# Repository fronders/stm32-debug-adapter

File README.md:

View this project on [CADLAB.io](https://cadlab.io/project/2519). 

# STM32 Debug Adapter Board

Adapter for various SWD programmers for STM32. 

<br />

This repo contains:
- Autodesk Eagle CAD v9 project
- PDF schematic & board layout
- Gerber files (in PCBWay-compatible format: RS-274X + Excellon)

What's here in README:
- [Supported STM32 programmers](#Supported-STM32-programmers)
- [Interfaces pinout](#Interfaces-pinout)
	- [Original ST-Link V2 by STMicroelectronics](#Original-ST-Link-V2-by-STMicroelectronics)
	- [J-Link by SEGGER](#J-Link-by-SEGGER)
	- [Chinese ST-Link V2 dongle](#Chinese-ST-Link-V2-dongle)
	- [Chinese MX-Link dongle](#Chinese-MX-Link-dongle)
	- [Nucleo-32 original ST-Link V2-1 by STMicroelectronics](#Nucleo-32-original-ST-Link-V2-1-by-STMicroelectronics)
	- [Nucleo-64 original ST-Link V2-1 by STMicroelectronics](#Nucleo-64-original-ST-Link-V2-1-by-STMicroelectronics)
	- [Nucleo-144 original ST-Link V2-1 by STMicroelectronics](#Nucleo-144-original-ST-Link-V2-1-by-STMicroelectronics)
	- [Blue Pill board (STM32F103C8T6)](#Blue-Pill-board-(STM32F103C8T6))
	- [Black Pill board (STM32F103C8T6)](#Black-Pill-board-(STM32F103C8T6))
	- [Tag-Connect 6 Pin Cable (TC2030-IDC)](#Tag-Connect-6-Pin-Cable-(TC2030-IDC))
- [Rev. B board info](#Rev.-B-board-info-(latest))
- [Rev. A board info](#Rev.-A-board-info)
- [Original board info](#Original-board-info)

<hr />

## Supported STM32 programmers

- Original ST-Link V2 by STMicroelectronics
- Nucleo original ST-Link V2-1 by STMicroelectronics
- Chinese ST-Link V2 clones (2 versions: ST-Link & MX-Link - different pinouts)
- J-Link by SEGGER

<hr />

## Interfaces pinout

### Original ST-Link V2 by STMicroelectronics

STM32 connector pinout:

| Name | Pin | Pin | Name |
| ---: | :---: | :---: | :--- |
| VDD_TRGT | 1 | 2 | VDD_TRGT |
| NC | 3 | 4 | GND |
| NC | 5 | 6 | GND |
| SWDIO | 7 | 8 | GND |
| SWCLK | 9 | 10 | GND |
| NC | 11 | 12 | GND |
| SWO | 13 | 14 | GND |
| NRST | 15 | 16 | GND |
| NC | 17 | 18 | GND |
| 3.3V | 19 | 20 | GND | 

### J-Link by SEGGER

Target connector pinout:

| Name | Pin | Pin | Name |
| ---: | :---: | :---: | :--- |
| 3.3V | 1 | 2 | NC |
| NC | 3 | 4 | GND |
| NC | 5 | 6 | GND |
| SWDIO | 7 | 8 | GND |
| SWCLK | 9 | 10 | GND |
| NC | 11 | 12 | GND |
| SWO | 13 | 14 | GND |
| NRST | 15 | 16 | GND |
| NC | 17 | 18 | GND |
| 5V | 19 | 20 | GND

### Chinese ST-Link V2 dongle

SWD connector pinout:

| Name | Pin | Pin | Name |
| ---: | :---: | :---: | :--- |
| RST\* | 1 | 2 | SWDIO |
| GND | 3 | 4 | GND |
| SWO\* | 5 | 6 | SWCLK |
| 3.3V | 7 | 8 | 3.3V |
| 5V\*\* | 9 | 10 | 5V\*\*

\* - not connected on the device, need to modify ST-Link: cut STM8's tracks for nRST & SWIM signals to become instead STM32's nRST (STM32 pin 18) & SWO (STM32 pin 31) signals

\*\* - not connected on adapter board

### Chinese MX-Link dongle

SWD connector pinout:

| Name | Pin | Pin | Name |
| ---: | :---: | :---: | :--- |
| RST\* | 1 | 2 | SWCLK |
| SWO\* | 3 | 4 | SWDIO |
| GND | 5 | 6 | GND |
| 3.3V | 7 | 8 | 3.3V |
| 5V\*\* | 9 | 10 | 5V\*\*

\* - not connected on the device, need to modify MX-Link: cut STM8's tracks for nRST & SWIM signals to become instead STM32's nRST (STM32 pin 18) & SWO (STM32 pin 31) signals

\*\* - not connected on adapter

### Nucleo-32 original ST-Link V2-1 by STMicroelectronics

CN2 connector pinout:

| Name | Pin | Pin | Name |
| ---: | :---: | :---: | :--- |
| - | - | 5 | NC |
| 3.3V | 4 | 3 | SWCLK |
| GND | 2 | 1 | SWDIO

### Nucleo-64 original ST-Link V2-1 by STMicroelectronics

CN4 connector pinout:

| Pin | Name |
| ---: | :--- |
| 1 | VDD_TRGT |
| 2 | SWCLK |
| 3 | GND |
| 4 | SWDIO |
| 5 | NRST |
| 6 | SWO

### Nucleo-144 original ST-Link V2-1 by STMicroelectronics

CN6 connector pinout:

| Pin | Name |
| ---: | :--- |
| 1 | VDD_TRGT |
| 2 | SWCLK |
| 3 | GND |
| 4 | SWDIO |
| 5 | NRST |
| 6 | SWO

### Blue Pill board (STM32F103C8T6)

Programming connector pinout:

| Pin | Name |
| ---: | :--- |
| 1 | GND |
| 2 | SWCLK |
| 3 | SWDIO |
| 4 | 3.3V

### Black Pill board (STM32F103C8T6)

Programming connector pinout:

| Pin | Name |
| ---: | :--- |
| 1 | GND |
| 2 | SWCLK |
| 3 | SWDIO |
| 4 | 3.3V

### Tag-Connect 6 Pin Cable (TC2030-IDC)

<br />

IDC-6 connector pinout:

| Name | Pin | Pin | Name |
| ---: | :---: | :---: | :--- |
| 3.3V | 1 | 2 | SWDIO |
| NRST | 3 | 4 | SWCLK |
| GND | 5 | 6 | SWO

<hr />

## Rev. B board info (latest)

PDF schematic & board:
- [Rev. B single file](pdf/rev.B/stm32%20debug%20adapter%20rev.B.pdf)
- [Rev. B schematic](pdf/rev.B/stm32%20debug%20adapter%20rev.B%20sch.pdf)
- [Rev. B board](pdf/rev.B/stm32%20debug%20adapter%20rev.B%20brd.pdf)

Solder jumper can be used with Original ST-Link to connect IDC-20 pin 19 VDD (3.3V) to rest of 3.3V (pins 1-2). **Jumper should remain open for use with J-Link, it has 3.3V output on pin 1, while pin 19 has 5V, might damage your board!**

Changes:
- Changed SWD pin header to match Nucleo ST-Link V2-1 pinout
- Fixed Blue Pill / Black Pill board (STM32F103C8T6) connector to be non-mirrored
- Added a solder jumper (NO) between pin 19 and pins 1-2 for Original ST-Link V2 to provide 3.3V power
- Added power indicator LED

Supported interfaces:
- Chinese ST-Link V2 dongle
- Chinese MX-Link dongle
- J-Link / Original ST-Link V2
- Tag-Connect (TC2030-IDC)
- Nucleo original ST-Link V2-1
- Blue Pill / Black Pill board

Known issues:
- none

<hr />

## Rev. A board info

PDF schematic & board:
- [Rev. A single file](pdf/rev.A/stm32%20debug%20adapter%20rev.A.pdf)
- [Rev. A schematic](pdf/rev.A/stm32%20debug%20adapter%20rev.A%20sch.pdf)
- [Rev. A board](pdf/rev.A/stm32%20debug%20adapter%20rev.A%20brd.pdf)

Changes:
- Added Blue Pill / Black Pill board (STM32F103C8T6) connector

Supported interfaces:
- Chinese ST-Link V2 dongle
- Chinese MX-Link dongle
- J-Link / Original ST-Link V2
- Tag-Connect (TC2030-IDC)
- SWD pin header
- Blue Pill / Black Pill board

Known issues:
- Blue Pill header mirrored, **need to plug in board upside down (chip facing down)**
- Original ST-Link V2 does not provide 3.3V on pins 1-2 (it is VDD_Target input instead), need to connect pin 19 to pins 1-2 on IDC-20 connector with external wire. J-Link works okay, as pin 1 has 3.3V output.

<hr />

## Original board info

PDF schematic & board:
- [Original schematic](pdf/original/stm32%20debug%20adapter%20sch.pdf)

Supported interfaces:
- Chinese ST-Link V2 dongle
- Chinese MX-Link dongle
- J-Link / Original ST-Link V2
- Tag-Connect (TC2030-IDC)
- SWD pin header

Known issues:
- Original ST-Link V2 does not provide 3.3V on pins 1-2 (it is VDD_Target input instead), need to connect pin 19 to pins 1-2 on IDC-20 connector with external wire. J-Link works okay, as pin 1 has 3.3V output.

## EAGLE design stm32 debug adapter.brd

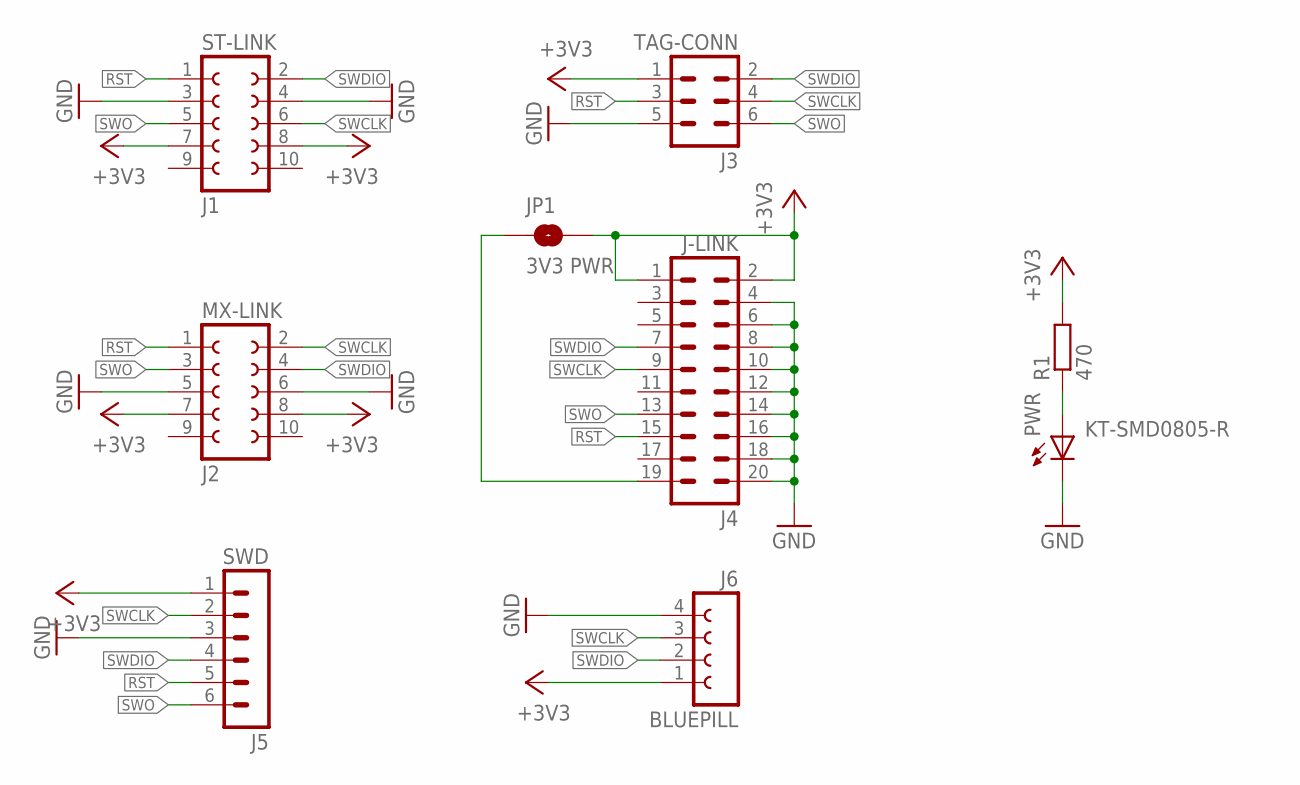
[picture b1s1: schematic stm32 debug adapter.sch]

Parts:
J1: ST-LINK; FE05-2W
J2: MX-LINK; FE05-2W
J3: TAG-CONN; ML6
J4: J-LINK; ML20
J5: SWD; MA06-1
J6: BLUEPILL; FE04W
JP1: 3V3 PWR; SMT-JUMPER_2_NO_NO-SILK
PWR: KT-SMD0805-R; SML0805
R1: 470; R0805

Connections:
3V3PWR: J4.19, JP1.1
+3V3: J1.7, J1.8, J2.7, J2.8, J3.1, J4.1, J4.2, J5.1, J6.1, JP1.2, R1.2
GND: J1.3, J1.4, J2.5, J2.6, J3.5, J4.4, J4.6, J4.8, J4.10, J4.12, J4.14, J4.16, J4.18, J4.20, J5.3, J6.4, PWR.C
unnamed: PWR.A, R1.1
RST: J1.1, J2.1, J3.3, J4.15, J5.5
SWCLK: J1.6, J2.2, J3.4, J4.9, J5.2, J6.3
SWDIO: J1.2, J2.4, J3.2, J4.7, J5.4, J6.2
SWO: J1.5, J2.3, J3.6, J4.13, J5.6

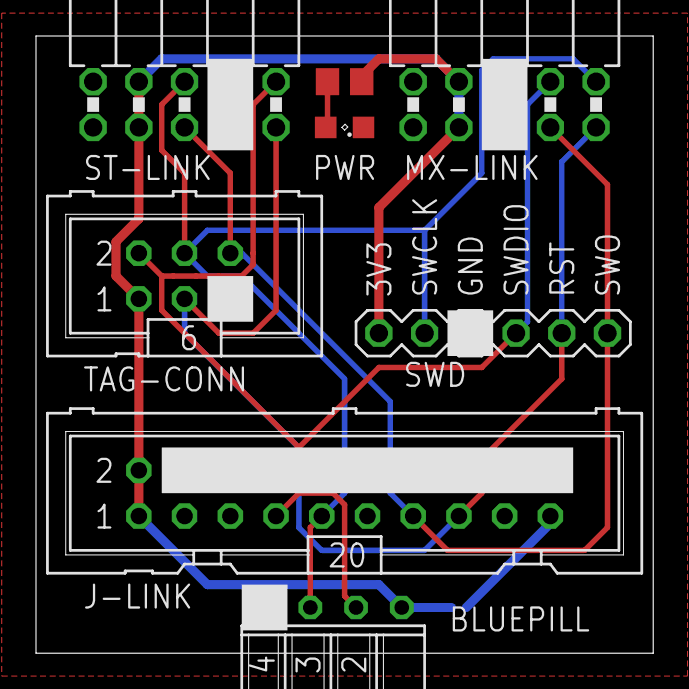
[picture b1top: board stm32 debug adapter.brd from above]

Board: 2 copper layers, 34.3 x 34.3 mm, 9 parts (1 on the bottom side), 8 nets.

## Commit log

2018-09-15 added original schematic + gerber files
2018-09-15 added rev.A schematic + board + gerber + pdf files
2018-09-15 added rev.B schematic + board + gerber + pdf files
2018-09-15 updated README with programmers list, interfaces pinout, changelogs
2018-09-15 fixed README
2018-09-15 fixed README tables
2018-09-15 fixed README pinout tables
2018-09-15 updated README: board pics & pdf links
2020-02-24 Backlink to CADLAB.io has been added.

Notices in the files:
parts and their libraries:
SparkFun-Jumpers: Licensing: Creative Commons ShareAlike 4.0 International - https://creativecommons.org/licenses/by-sa/4.0
